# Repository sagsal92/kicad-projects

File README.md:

# kicad-projects
kicad projects done by me

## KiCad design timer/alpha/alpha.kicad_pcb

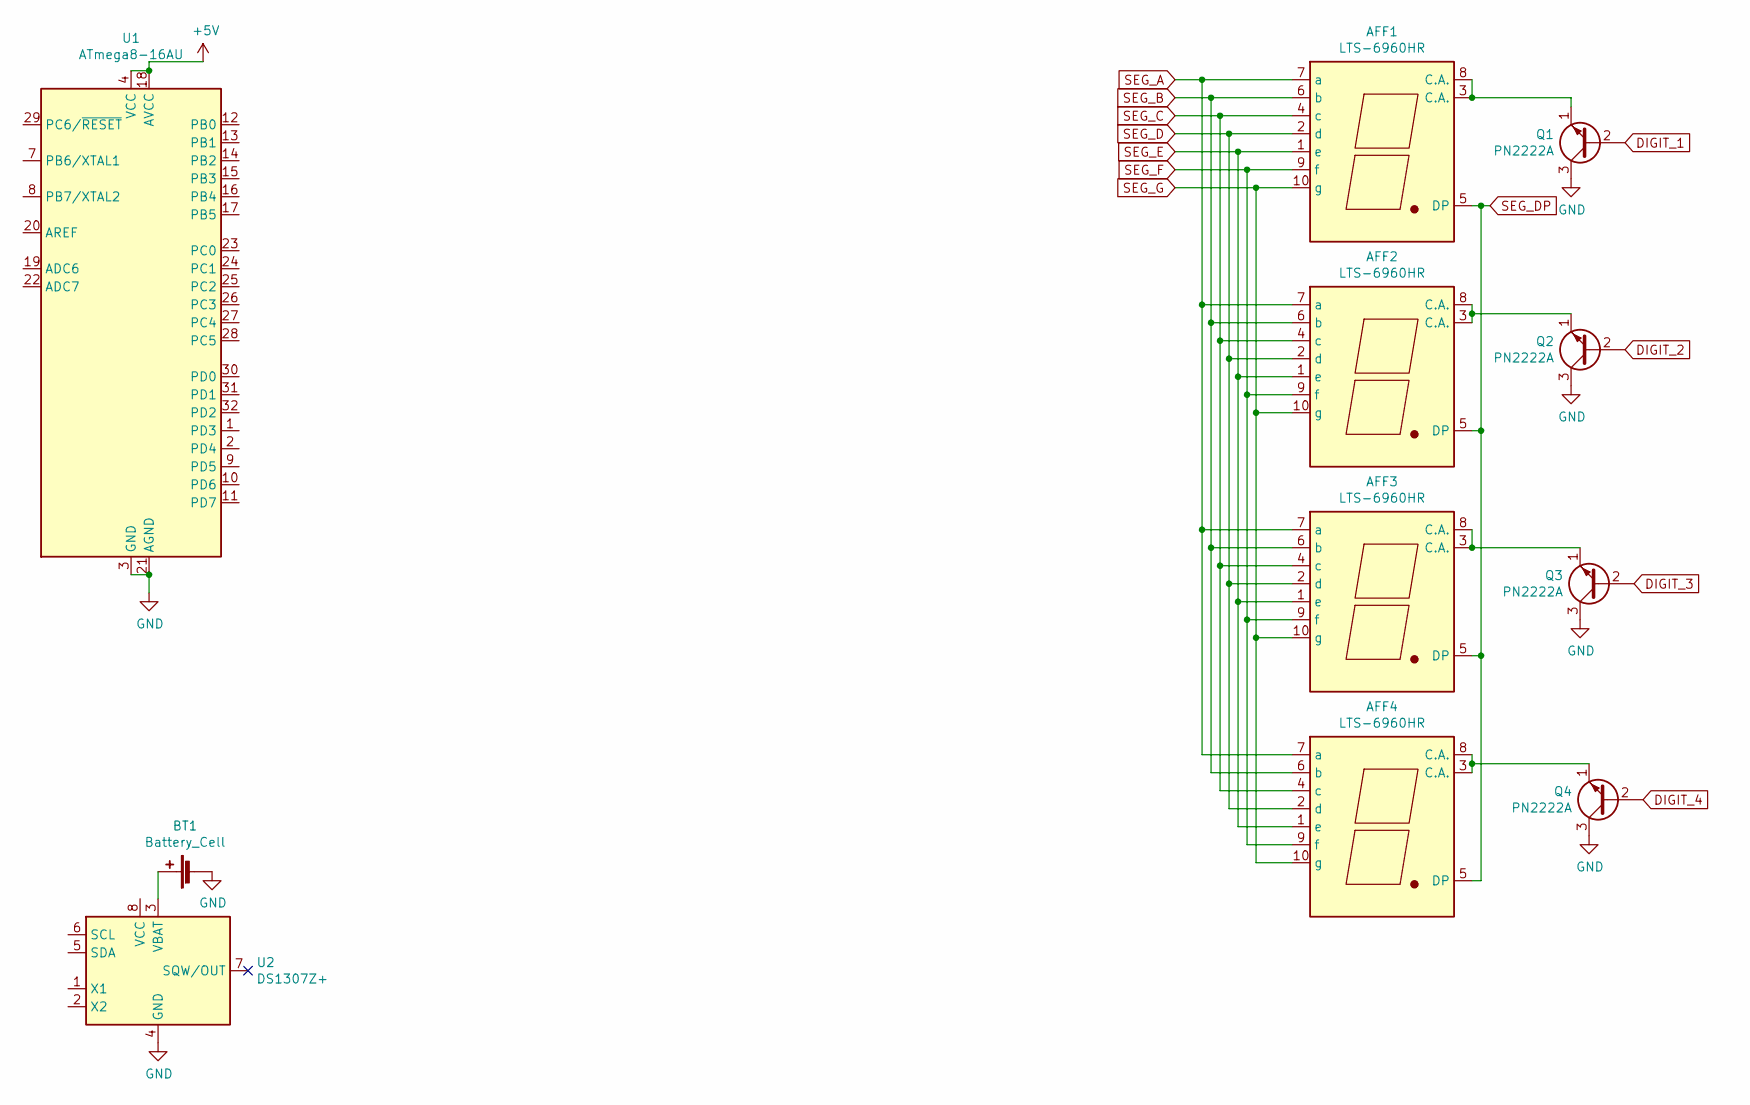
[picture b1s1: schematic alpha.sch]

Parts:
AFF1, AFF2, AFF3, AFF4: LTS-6960HR; 7SegmentLED_LTS6760_LTS6780
BT1: Battery_Cell
Q1, Q2, Q3, Q4: PN2222A; TO-92_Inline
U1: ATmega8-16AU; TQFP-32_7x7mm_P0.8mm
U2: DS1307Z+; SOIC-8_3.9x4.9mm_P1.27mm

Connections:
+5V: U1.4 (VCC), U1.6 (VCC), U1.18 (AVCC)
DIGIT_1: Q1.2 (B)
DIGIT_2: Q2.2 (B)
DIGIT_3: Q3.2 (B)
DIGIT_4: Q4.2 (B)
GND: BT1.2 (-), Q1.3 (C), Q2.3 (C), Q3.3 (C), Q4.3 (C), U1.3 (GND), U1.5 (GND), U1.21 (AGND), U2.4 (GND)
unnamed: AFF1.3 (C.A.), AFF1.8 (C.A.), Q1.1 (E)
unnamed: AFF2.3 (C.A.), AFF2.8 (C.A.), Q2.1 (E)
unnamed: AFF3.3 (C.A.), AFF3.8 (C.A.), Q3.1 (E)
unnamed: AFF4.3 (C.A.), AFF4.8 (C.A.), Q4.1 (E)
unnamed: BT1.1 (+), U2.3 (VBAT)
SEG_A: AFF1.7 (a), AFF2.7 (a), AFF3.7 (a), AFF4.7 (a)
SEG_B: AFF1.6 (b), AFF2.6 (b), AFF3.6 (b), AFF4.6 (b)
SEG_C: AFF1.4 (c), AFF2.4 (c), AFF3.4 (c), AFF4.4 (c)
SEG_D: AFF1.2 (d), AFF2.2 (d), AFF3.2 (d), AFF4.2 (d)
SEG_DP: AFF1.5 (DP), AFF2.5 (DP), AFF3.5 (DP), AFF4.5 (DP)
SEG_E: AFF1.1 (e), AFF2.1 (e), AFF3.1 (e), AFF4.1 (e)
SEG_F: AFF1.9 (f), AFF2.9 (f), AFF3.9 (f), AFF4.9 (f)
SEG_G: AFF1.10 (g), AFF2.10 (g), AFF3.10 (g), AFF4.10 (g)

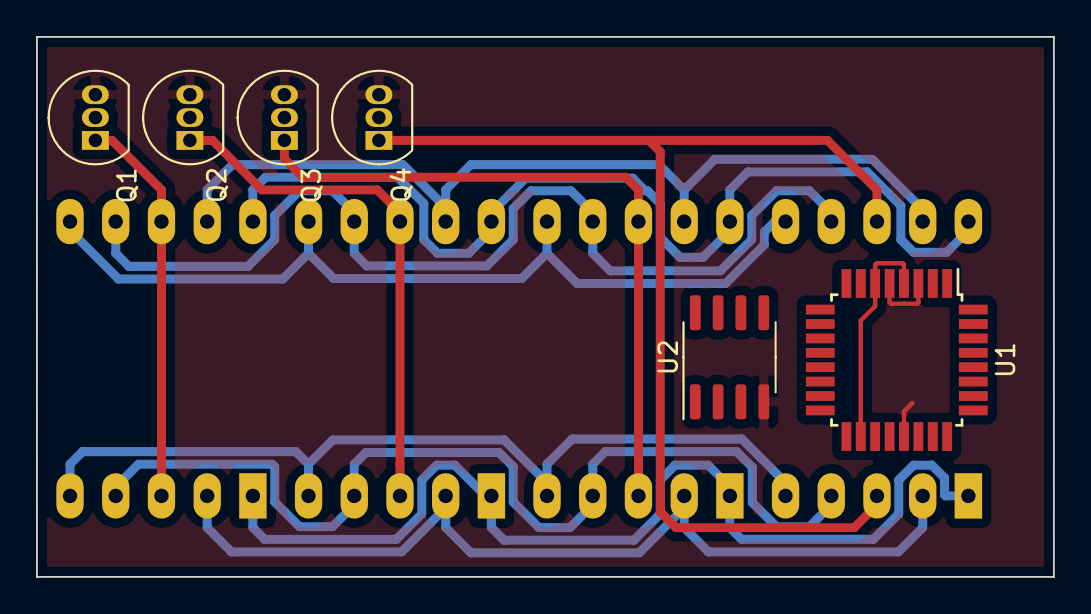
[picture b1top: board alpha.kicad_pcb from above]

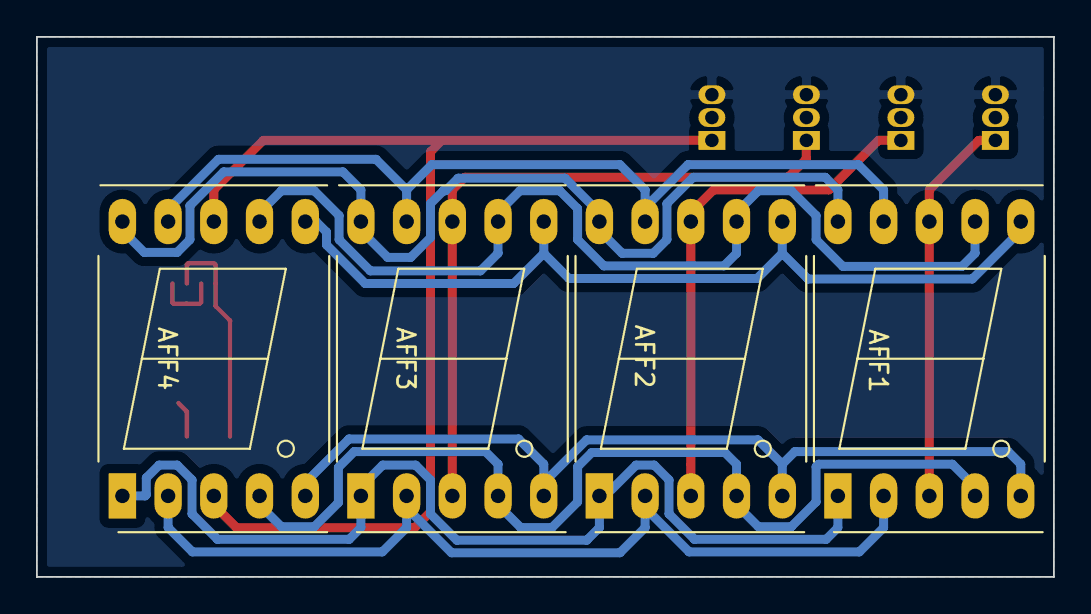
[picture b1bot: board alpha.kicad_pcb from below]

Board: 2 copper layers, 56.5 x 30.0 mm, 10 parts (4 on the bottom side), 14 nets.

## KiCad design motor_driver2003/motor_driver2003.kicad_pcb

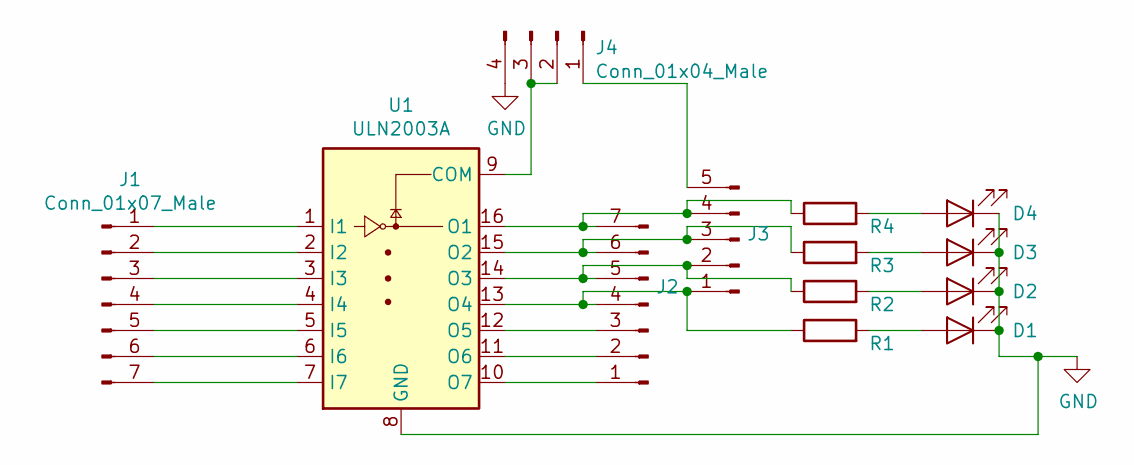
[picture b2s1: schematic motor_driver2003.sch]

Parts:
D1, D2, D3, D4: LED; LED_0805_2012Metric_Pad1.15x1.40mm_HandSolder
J1, J2: Conn_01x07_Male; PinHeader_1x07_P2.54mm_Vertical
J3: Conn_01x05_Male; PinHeader_1x05_P2.54mm_Vertical
J4: Conn_01x04_Male; PinHeader_1x04_P2.54mm_Vertical
R1, R2, R3, R4: R; R_0805_2012Metric_Pad1.15x1.40mm_HandSolder
U1: ULN2003A; SOIC-16_3.9x9.9mm_P1.27mm

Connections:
GND: D1.1 (K), D2.1 (K), D3.1 (K), D4.1 (K), J4.4, U1.8 (GND)
unnamed: D1.2 (A), R1.2
unnamed: D2.2 (A), R2.2
unnamed: D3.2 (A), R3.2
unnamed: D4.2 (A), R4.2
unnamed: J1.1, U1.1 (I1)
unnamed: J1.2, U1.2 (I2)
unnamed: J1.3, U1.3 (I3)
unnamed: J1.4, U1.4 (I4)
unnamed: J1.5, U1.5 (I5)
unnamed: J1.6, U1.6 (I6)
unnamed: J1.7, U1.7 (I7)
unnamed: J2.1, U1.10 (O7)
unnamed: J2.2, U1.11 (O6)
unnamed: J2.3, U1.12 (O5)
unnamed: J2.4, J3.1, R1.1, U1.13 (O4)
unnamed: J2.5, J3.2, R2.1, U1.14 (O3)
unnamed: J2.6, J3.3, R3.1, U1.15 (O2)
unnamed: J2.7, J3.4, R4.1, U1.16 (O1)
unnamed: J3.5, J4.1
unnamed: J4.2, J4.3, U1.9 (COM)

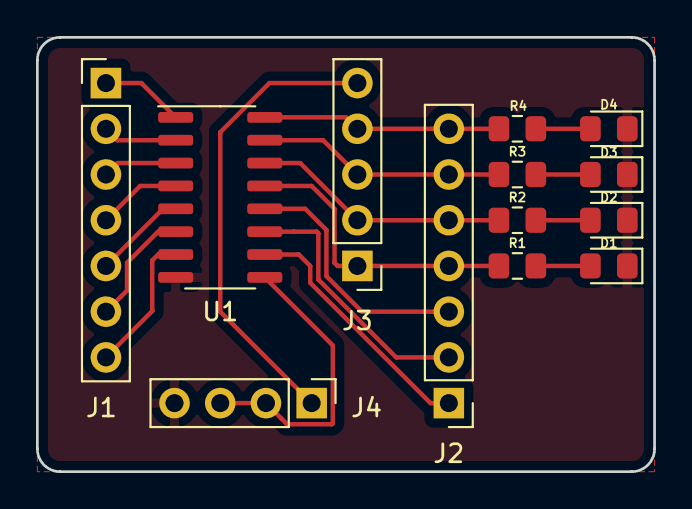
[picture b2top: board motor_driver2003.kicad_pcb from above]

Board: 2 copper layers, 34.3 x 24.1 mm, 13 parts (0 on the bottom side), 21 nets.
